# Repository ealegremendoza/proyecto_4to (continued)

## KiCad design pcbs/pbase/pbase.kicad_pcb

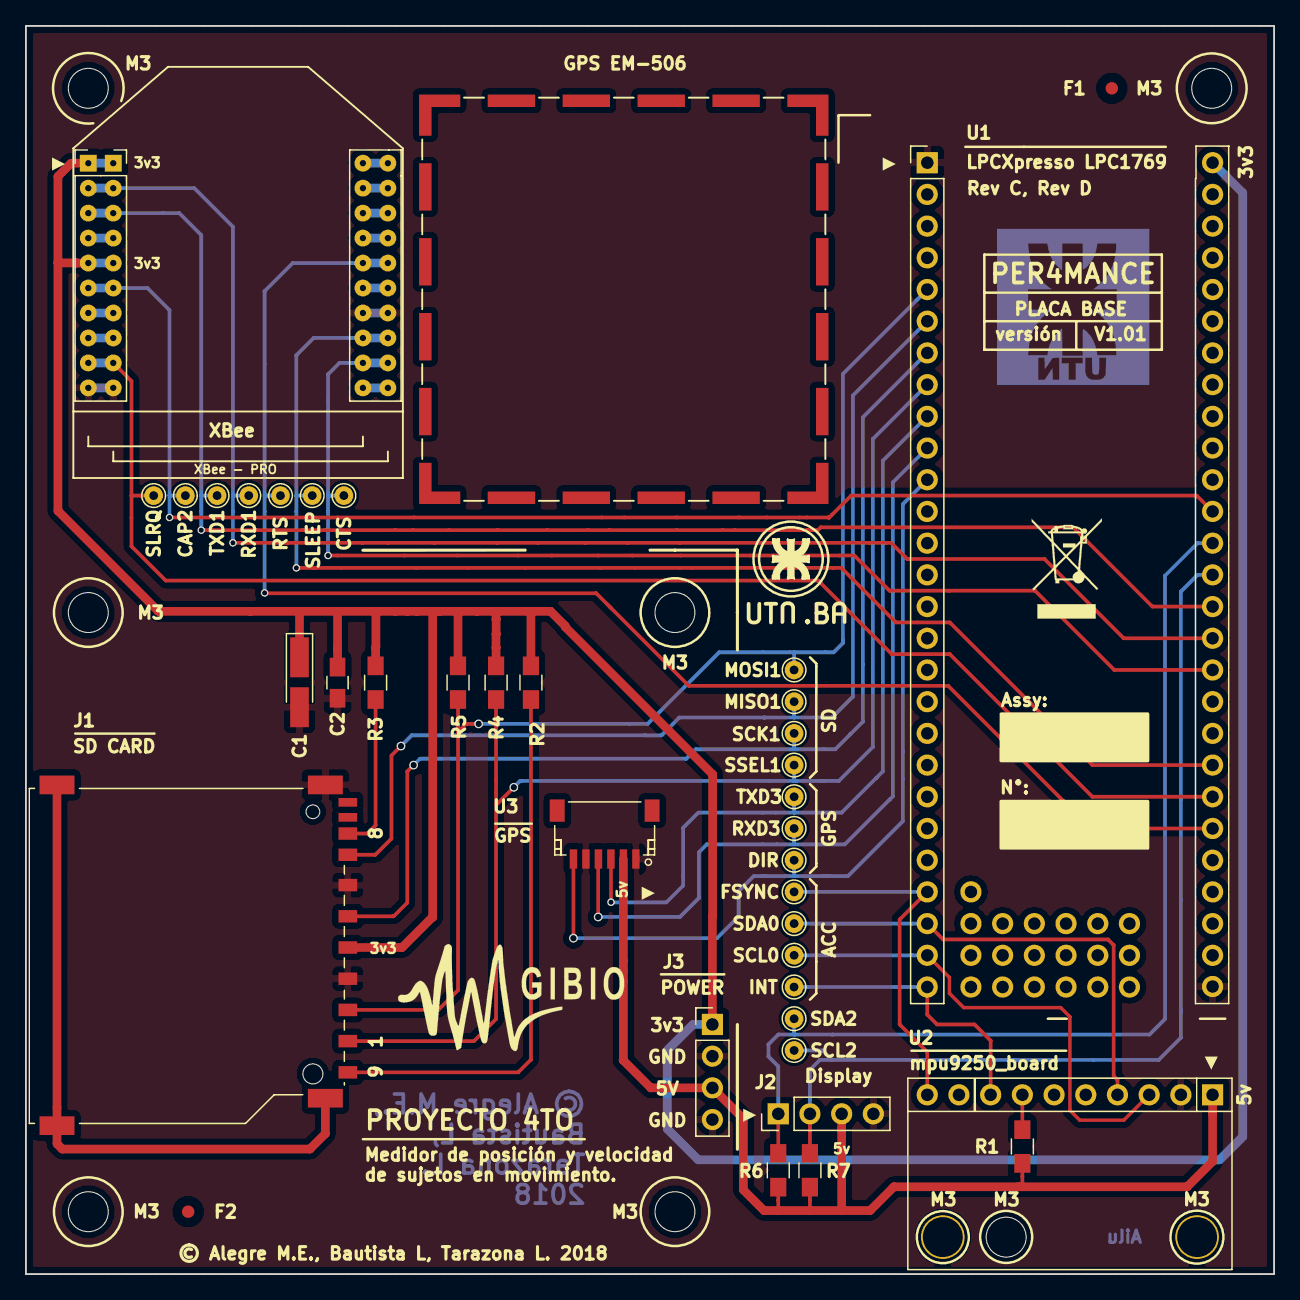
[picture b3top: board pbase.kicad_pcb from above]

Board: 2 copper layers, 100.0 x 100.0 mm, 46 parts (0 on the bottom side), 26 nets.

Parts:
C1: 1uF x 16V; CP_Tantalum_Case-A_EIA-3216-18_Hand
C2: 100n; C_0805_HandSoldering
CAP2: CAP2; TestPoint_THTPad_D1.5mm_Drill0.7mm
CTS: CTS1; TestPoint_THTPad_D1.5mm_Drill0.7mm
DIR: DIR; TestPoint_THTPad_D1.5mm_Drill0.7mm
F1, F2: Fiducial_1mm_Dia_2.54mm_Outer_CopperTop
FSYNC: FSYNC; TestPoint_THTPad_D1.5mm_Drill0.7mm
GPS EM-506: Laird_Technologies_BMI-S-204-F_32.00x32.00mm
INT: INT; TestPoint_THTPad_D1.5mm_Drill0.7mm
J1: SD_Card; SD_TE_2041021_edit
J2, J3: Conn_01x04; Socket_Strip_Straight_1x04_Pitch2.54mm
M3, M3#2, M3#3, M3#4, M3#5, M3#6, M3#7: MountingHole_3.2mm_M3_DIN965
MISO1: MISO1; TestPoint_THTPad_D1.5mm_Drill0.7mm
MOD1: XB24CZ7PIT-004; xbee_xb24cz7pit_004
MOSI1: MOSI1; TestPoint_THTPad_D1.5mm_Drill0.7mm
R1: 0R; R_0805_HandSoldering
R2, R3: 10K; R_0805_HandSoldering
R4, R5: 33K; R_0805_HandSoldering
R6: RD1; R_0805_HandSoldering
R7: RD2; R_0805_HandSoldering
RTS: RTS1; TestPoint_THTPad_D1.5mm_Drill0.7mm
RXD1: RXD1; TestPoint_THTPad_D1.5mm_Drill0.7mm
RXD3: RXD3; TestPoint_THTPad_D1.5mm_Drill0.7mm
SCK1: SCK1; TestPoint_THTPad_D1.5mm_Drill0.7mm
SCL0: SCL0; TestPoint_THTPad_D1.5mm_Drill0.7mm
SCL2: SCL2; TestPoint_THTPad_D1.5mm_Drill0.7mm
SDA0: SDA0; TestPoint_THTPad_D1.5mm_Drill0.7mm
SDA2: SDA2; TestPoint_THTPad_D1.5mm_Drill0.7mm
SLEEP: SLEEP; TestPoint_THTPad_D1.5mm_Drill0.7mm
SLRQ: SRQ; TestPoint_THTPad_D1.5mm_Drill0.7mm
SSEL1: SSEL1; TestPoint_THTPad_D1.5mm_Drill0.7mm
TXD1: TXD1; TestPoint_THTPad_D1.5mm_Drill0.7mm
TXD3: TXD3; TestPoint_THTPad_D1.5mm_Drill0.7mm
U1: LPCXpresso_LPC1769_revB; lpc1769_board_revC
U2: acc_mpu9250_board; mpu9250_board
U3: GPS_EM506; JST_SH_SM06B-SRSS-TB_06x1.00mm_Angled

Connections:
+3V3: C1.1, C2.1, J1.4, J3.1, MOD1.1, MOD1.5, R2.1, R3.1, R4.1, R5.1, U1.J-28
+5V: J2.3, J3.3, R1.1, R6.1, R7.1, U2.1, U3.2
/Display/SCL2: J2.2, R7.2, SCL2.1, U1.J-41
/Display/SDA2: J2.1, R6.2, SDA2.1, U1.J-40
/GPS/DIR: DIR.1, U1.J-11, U3.6
/GPS/RXD3: RXD3.1, U1.J-10, U3.4
/GPS/TXD3: TXD3.1, U1.J-9, U3.3
/TarjetaSD/MISO1: J1.7, MISO1.1, U1.J-6
/TarjetaSD/MOSI1: J1.2, MOSI1.1, R5.2, U1.J-5
/TarjetaSD/SCK1: J1.5, SCK1.1, U1.J-7
/TarjetaSD/SSEL1: J1.1, R4.2, SSEL1.1, U1.J-8
/TarjetaSD/data1: J1.8, R3.2
/TarjetaSD/data2: J1.9, R2.2
/Zigbee/CTS: CTS.1, MOD1.12, U1.J-44
/Zigbee/RTS: MOD1.16, RTS.1, U1.J-49
/Zigbee/RXD1: MOD1.2, RXD1.1, U1.J-43
/Zigbee/SLEEP: MOD1.13, SLEEP.1, U1.J-47
/Zigbee/SLRQ: MOD1.9, SLRQ.1, U1.J-48
/Zigbee/TXD1: MOD1.3, TXD1.1, U1.J-42
/acc/FSYNC: FSYNC.1, U1.J-24, U2.10
/acc/INT: INT.1, U1.J-27, U2.8
/acc/SCL0: SCL0.1, U1.J-26, U2.3
/acc/SDA0: SDA0.1, U1.J-25, U2.4
/lpc1769/CAP2.1: CAP2.1, MOD1.6, U1.J-39
GND: C1.2, C2.2, J1.3, J1.6, J1.12, J2.4, J3.2, J3.4, MOD1.10, MOD1.14, U1.J-1, U1.J-54, U2.2, U3.1, U3.5
unnamed: R1.2, U2.7

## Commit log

2018-07-10 inicio
2018-07-10 cambios en mirama
2018-07-10 Modificación en las funciones de los botones que actualizan los valores medios. Se separó en un archivo a parte la clase MyApp_class() -> MyApp.py
2018-07-10 ahora los botones funcionan.
2018-07-15 cambio de carpetas
2018-07-15 se modificaron los nombres de las subcarpetas del direcotrio docs
2018-07-16 modificacion del codigo. se paracion en carpetas para un mejor desarrollo. Aun faltan corregir bugs pero anda.
2018-07-16 cambios en DSP.py y se agrega archivo example4.py en la carpeta de Leandro. Ya se actualizó el código para funcionar con la nueva clase.
2018-07-16 modificacion de DSP.py
2018-07-17 cambios en pycache
2018-07-17 README update
2018-07-19 Add files via upload
    Se agrega ejemplo inicial de señal de gps con un filtro fir pasa bajos de orden 10 y su respuesta en frecuencia
2018-07-20 modificaciones en gps_ej_1.py
2018-07-20 se modificó la forma de acceder al archivo *.csv
2018-08-09 Se intentó hacer un ejecutable de app.py usando chmod +x app.py
2018-08-13 Modificación a README. Se agrega carpeta pcb
2018-08-13 Creado simbolo de LPCXpresso LPC1769 rev B, KiCad
2018-08-14 se agrega simbolo de LPC1769 revD
2018-08-14 Cambio el nombre de la carpeta lpcxpresso_lpc1769_revb -> lpcxpresso_lpc1769
2018-08-14 Modificación del pinout de todos los simbolos
2018-08-14 Borrada carpeta modulo_GPS_ublox, usamos otro modulo
2018-08-14 Se agrega simbolo gps_em506
2018-08-14 Agregada info del LPCXpresso
2018-08-14 Agregado simbolo de acelerometro acc_mu6050 y modificados los demas simbolos
2018-08-14 modificado acc_mu6050
2018-08-14 eliminados archivos basura
2018-08-18 cambios en ordenamiento de subcarpetas
2018-08-19 Cambios en lucas
2018-08-20 New Ezequiel/serie_tests
2018-08-21 Cambios en carpeta sch
2018-08-26 cambios sch
2018-08-26 archivo de prueba
2018-08-26 SCH update
2018-08-26 code update
2018-08-31 ezequiel update
2018-08-31 ezequiel update pdf
2018-09-04 add lpc1769 stick footprints
2018-09-05 add zigbee
2018-09-05 agrego dimensiones del xbee
2018-09-09 borrado sch
2018-09-09 sch_v1.0 init
2018-09-09 sch_v1.0 first update
2018-09-10 primera finalizacion del esquemático de pbase
2018-09-11 updata
2018-09-11 update 11 sep
2018-09-11 update pngs
2018-09-13 Test points
2018-09-13 pngs
2018-09-13 cambios a sch
2018-09-15 agregado sch gy521
2018-09-17 modificaciones varias al acc mpu-6050
2018-09-17 modificadas librerias de acc
2018-09-17 update LEEME
2018-09-17 added mpu9250
2018-09-17 reemplazado acc por mpu9250
2018-09-17 sch annotate v1.1
2018-09-17 docs modulo gps info
2018-09-17 gps docs added
2018-09-18 agregados footprints gps y mpu9250
2018-09-19 pbase pcb inicio
2018-09-19 BOM agregado
2018-09-21 pbase edits
2018-09-21 PCB PLACING V1
2018-09-23 pcb replacing
2018-09-25 pcb fin 1
2018-09-26 pbase pcb finalizado v1
2018-09-27 pcb finalizado
2018-09-27 PCB correcion pista 3V3
2018-09-27 PLACA FINALIZADA
2018-09-30 movida carpeta lpc_info a docs
2018-09-30 pbase lpc drc
2018-10-01 pequeños cambios
2018-10-01 agregado footprint mpu9250
2018-10-01 cambiado footprint acc mpu9250, agregado mounting hole para mpu 6050
2018-10-01 pcb lpc finalizado sin llaves
2018-10-02 PCBs pbase y pbase-ino FINALIZADOS, archivos gerbers en zip dentro del directrio /pcbs
2018-10-12 pcb cargador
2018-10-26 LEEME UPDATE
2018-10-31 pdfs realizados
2018-10-31 agregados los BOM
2018-10-31 correcciones en el BOM
2018-10-31 pdfs de pcbs finalizados. Contienen SCH, PCB y BOM.
2018-11-01 correcciones en los pdfs de los pcb
2018-12-01 Add files via upload
    Archivos ejemplo de filtro de kalman con datos obtenidos en internet (datos también adjuntados).
2019-01-14 Add files via upload
    Ejemplos con el acelerómetro a 100Hz. Se utiliza un filtro de kalman para filtrar velocidad, aceleracion , velocidad y posicion angular, campo magnetico, y luego se utilizan esas mediciones para obte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
